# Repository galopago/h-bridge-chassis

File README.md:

# TARJETA PARA MANEJO DE DIRECCION DE MOTORES DC BASADA EN CHIP L293D

Este circuito cumple la funcion de conectar el circuito integrado para manejo
de direccion para motores DC L293 con un modulo receptor de radio control RX480E. Adicionalmente
la tarjeta sirve como chasis para soportar los motores, rueda libre y soporte para pilas.

## Como usar este repositorio?

El proyecto fue desarrollado en Kicad Version 5.1

## Estructura de carpetas

* El directorio principal o raiz contiene todos los archivos fuentes en Kicad: proyecto, esquematico y circuito impreso

* El directorio gerber contiene los archivos necesarios para la fabricacion de las tarjetas de circuito impreso.

* El directorio ensamble contiene los archivos para ensamble automatizado: Lista de materiales (BOM) y archivo de centroides.

* El directorio info contiene informacion adicional sobre la tarjeta en otros formatos como PDF e imagenes.

* El directorio library contiene simbolos esquematicos adicionales que no vienen en la instalacion por defecto de KiCad

* El directorio modules contiene footprints adicionales que no vienen en la instalacion por defecto de KiCad

## Licencia

Este es un proyecto de Hardware Libre y esta licenciado bajo [Creative Commons Attribution 4.0 International License](http://creativecommons.org/licenses/by/4.0/)

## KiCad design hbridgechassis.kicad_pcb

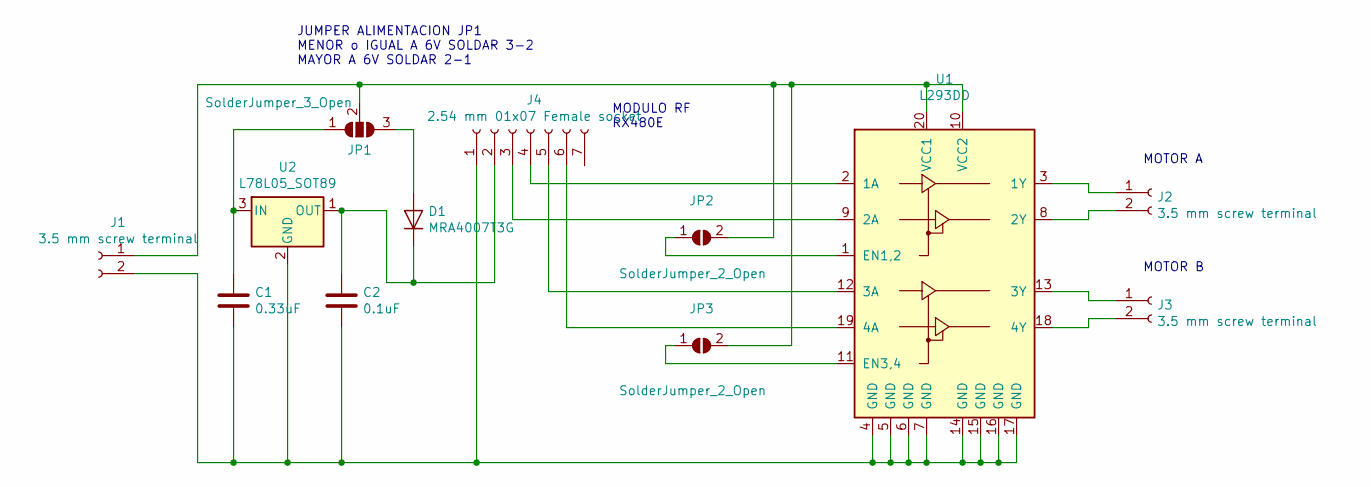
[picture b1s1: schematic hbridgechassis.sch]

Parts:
C1: 0.33uF; C_0805_2012Metric
C2: 0.1uF; C_0805_2012Metric
D1: MRA4007T3G; D_SMA
J1, J2, J3: 3.5 mm screw terminal; TerminalBlock_4Ucon_1x02_P3.50mm_Horizontal
J4: 2.54 mm 01x07 Female socket; PinSocket_1x07_P2.54mm_Vertical
JP1: SolderJumper_3_Open; SolderJumper-3_P1.3mm_Open_RoundedPad1.0x1.5mm_NumberLabels
JP2, JP3: SolderJumper_2_Open; SolderJumper-2_P1.3mm_Open_RoundedPad1.0x1.5mm
U1: L293DD; SO-20_12.8x7.5mm_P1.27mm
U2: L78L05_SOT89; SOT-89-3

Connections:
unnamed: C1.1, JP1.1 (A), U2.3 (IN)
unnamed: C1.2, C2.2, J1.2, J4.1, U1.4 (GND), U1.5 (GND), U1.6 (GND), U1.7 (GND), U1.14 (GND), U1.15 (GND), U1.16 (GND), U1.17 (GND), U2.2 (GND)
unnamed: C2.1, D1.1 (K), J4.2, U2.1 (OUT)
unnamed: D1.2 (A), JP1.3 (B)
unnamed: J1.1, JP1.2 (C), JP2.2 (B), JP3.2 (B), U1.10 (VCC2), U1.20 (VCC1)
unnamed: J2.1, U1.3 (1Y)
unnamed: J2.2, U1.8 (2Y)
unnamed: J3.1, U1.13 (3Y)
unnamed: J3.2, U1.18 (4Y)
unnamed: J4.3, U1.9 (2A)
unnamed: J4.4, U1.2 (1A)
unnamed: J4.5, U1.12 (3A)
unnamed: J4.6, U1.19 (4A)
unnamed: JP2.1 (A), U1.1 (EN1,2)
unnamed: JP3.1 (A), U1.11 (EN3,4)

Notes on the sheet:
MODULO RF RX480E
MOTOR A
MOTOR B
JUMPER ALIMENTACION JP1 MENOR o IGUAL A 6V SOLDAR 3-2 MAYOR A 6V SOLDAR 2-1

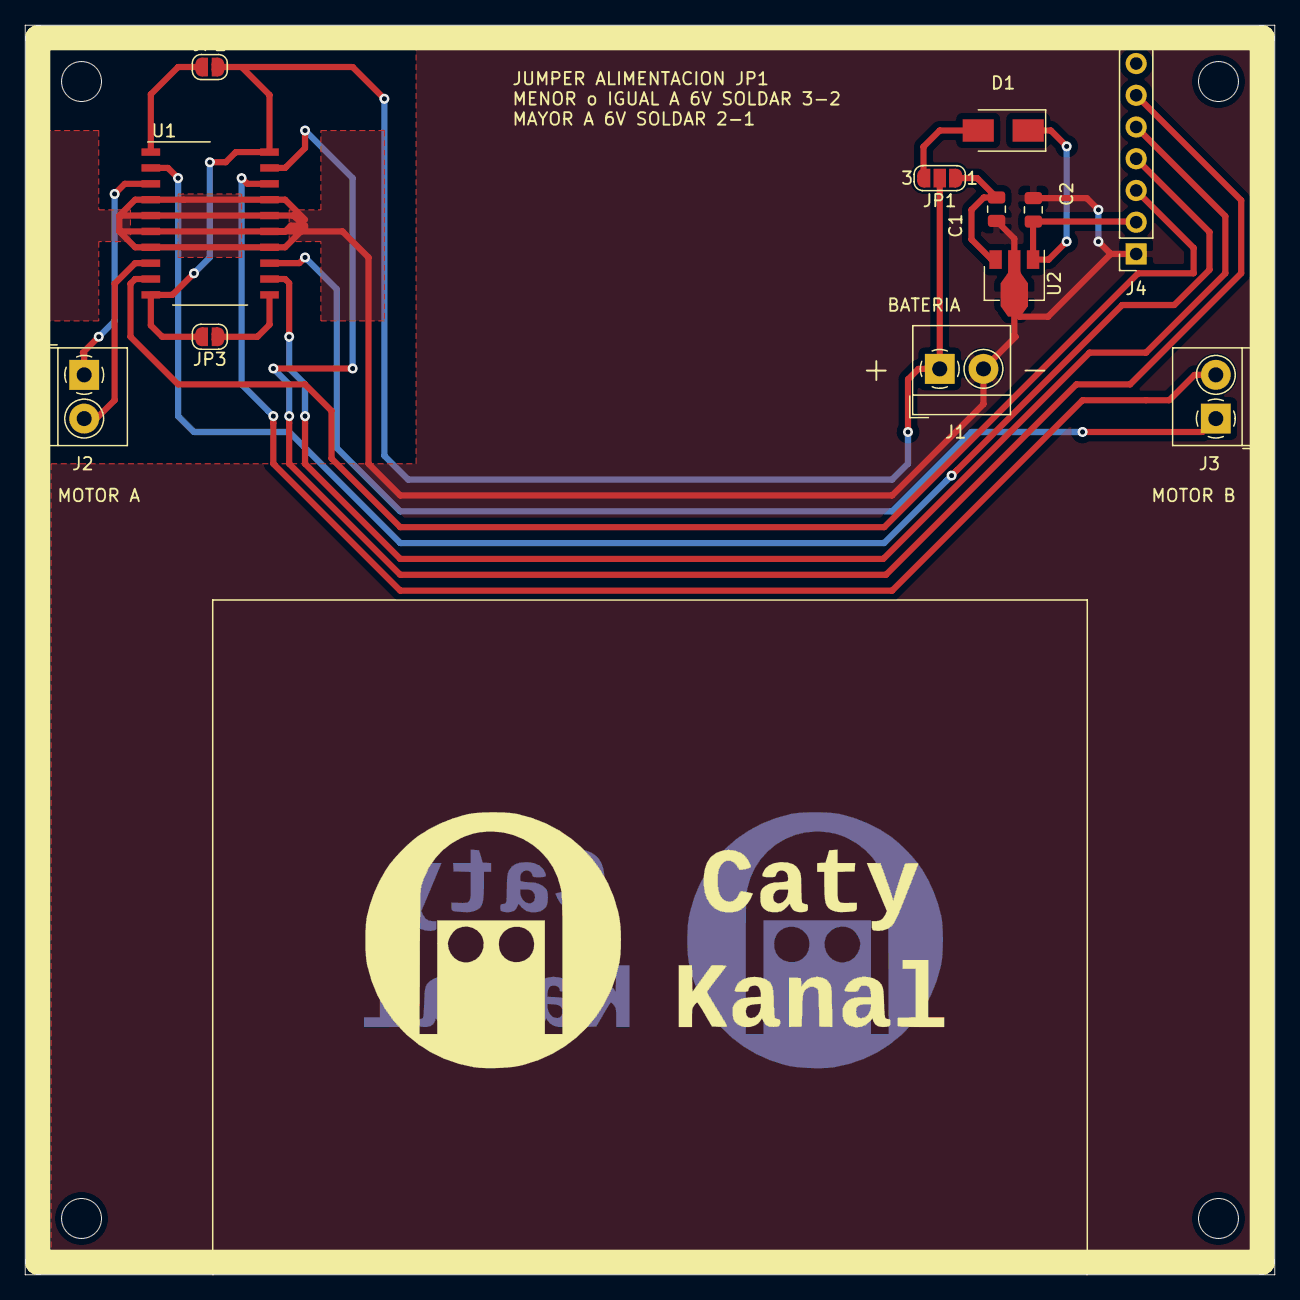
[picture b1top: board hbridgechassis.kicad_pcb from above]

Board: 2 copper layers, 100.0 x 100.0 mm, 16 parts (0 on the bottom side), 15 nets.

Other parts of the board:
M1, M2, M3, M4: MountingHole_3.2mm_M3

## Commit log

2021-01-21 primer commit
2021-01-21 creacion componente L293DD montaje superficial
2021-01-22 concepto inicial, esquematico y circuito impreso
2021-01-22 archivos adicionales info pdf
2021-01-22 agregados pdf de componentes
2021-01-25 agregado regulador 78l05 y condensadores
2021-02-04 enrutado preliminar de pistas y archivos de fabricacion
2021-02-09 Logo, areas de cobre y mejoras en serigrafia
